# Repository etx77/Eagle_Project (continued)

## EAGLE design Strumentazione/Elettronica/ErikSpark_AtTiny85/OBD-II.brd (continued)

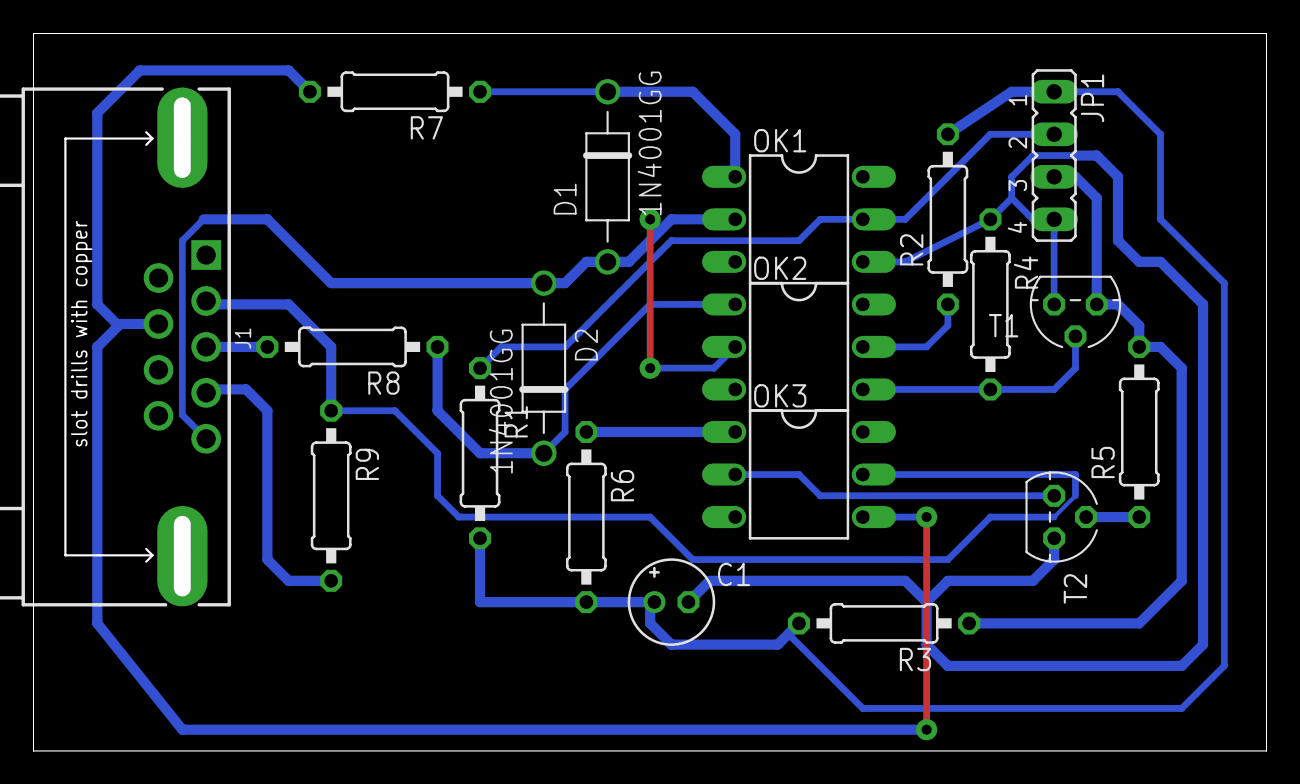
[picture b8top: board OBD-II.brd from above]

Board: 2 copper layers, 73.6 x 42.9 mm, 19 parts (0 on the bottom side), 16 nets.
